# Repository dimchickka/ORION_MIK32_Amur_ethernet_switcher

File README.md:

Типы команд, поддерживаемые устройством

:SWITH0 1;SWITH2 1;\*OPC? - переключение нулевого реле в позицию 1, второго реле в позицию 1

:CHECK ALL;\*OPC? проверка всех реле

:CHECK 1;\*OPC?  -проверка реле 1

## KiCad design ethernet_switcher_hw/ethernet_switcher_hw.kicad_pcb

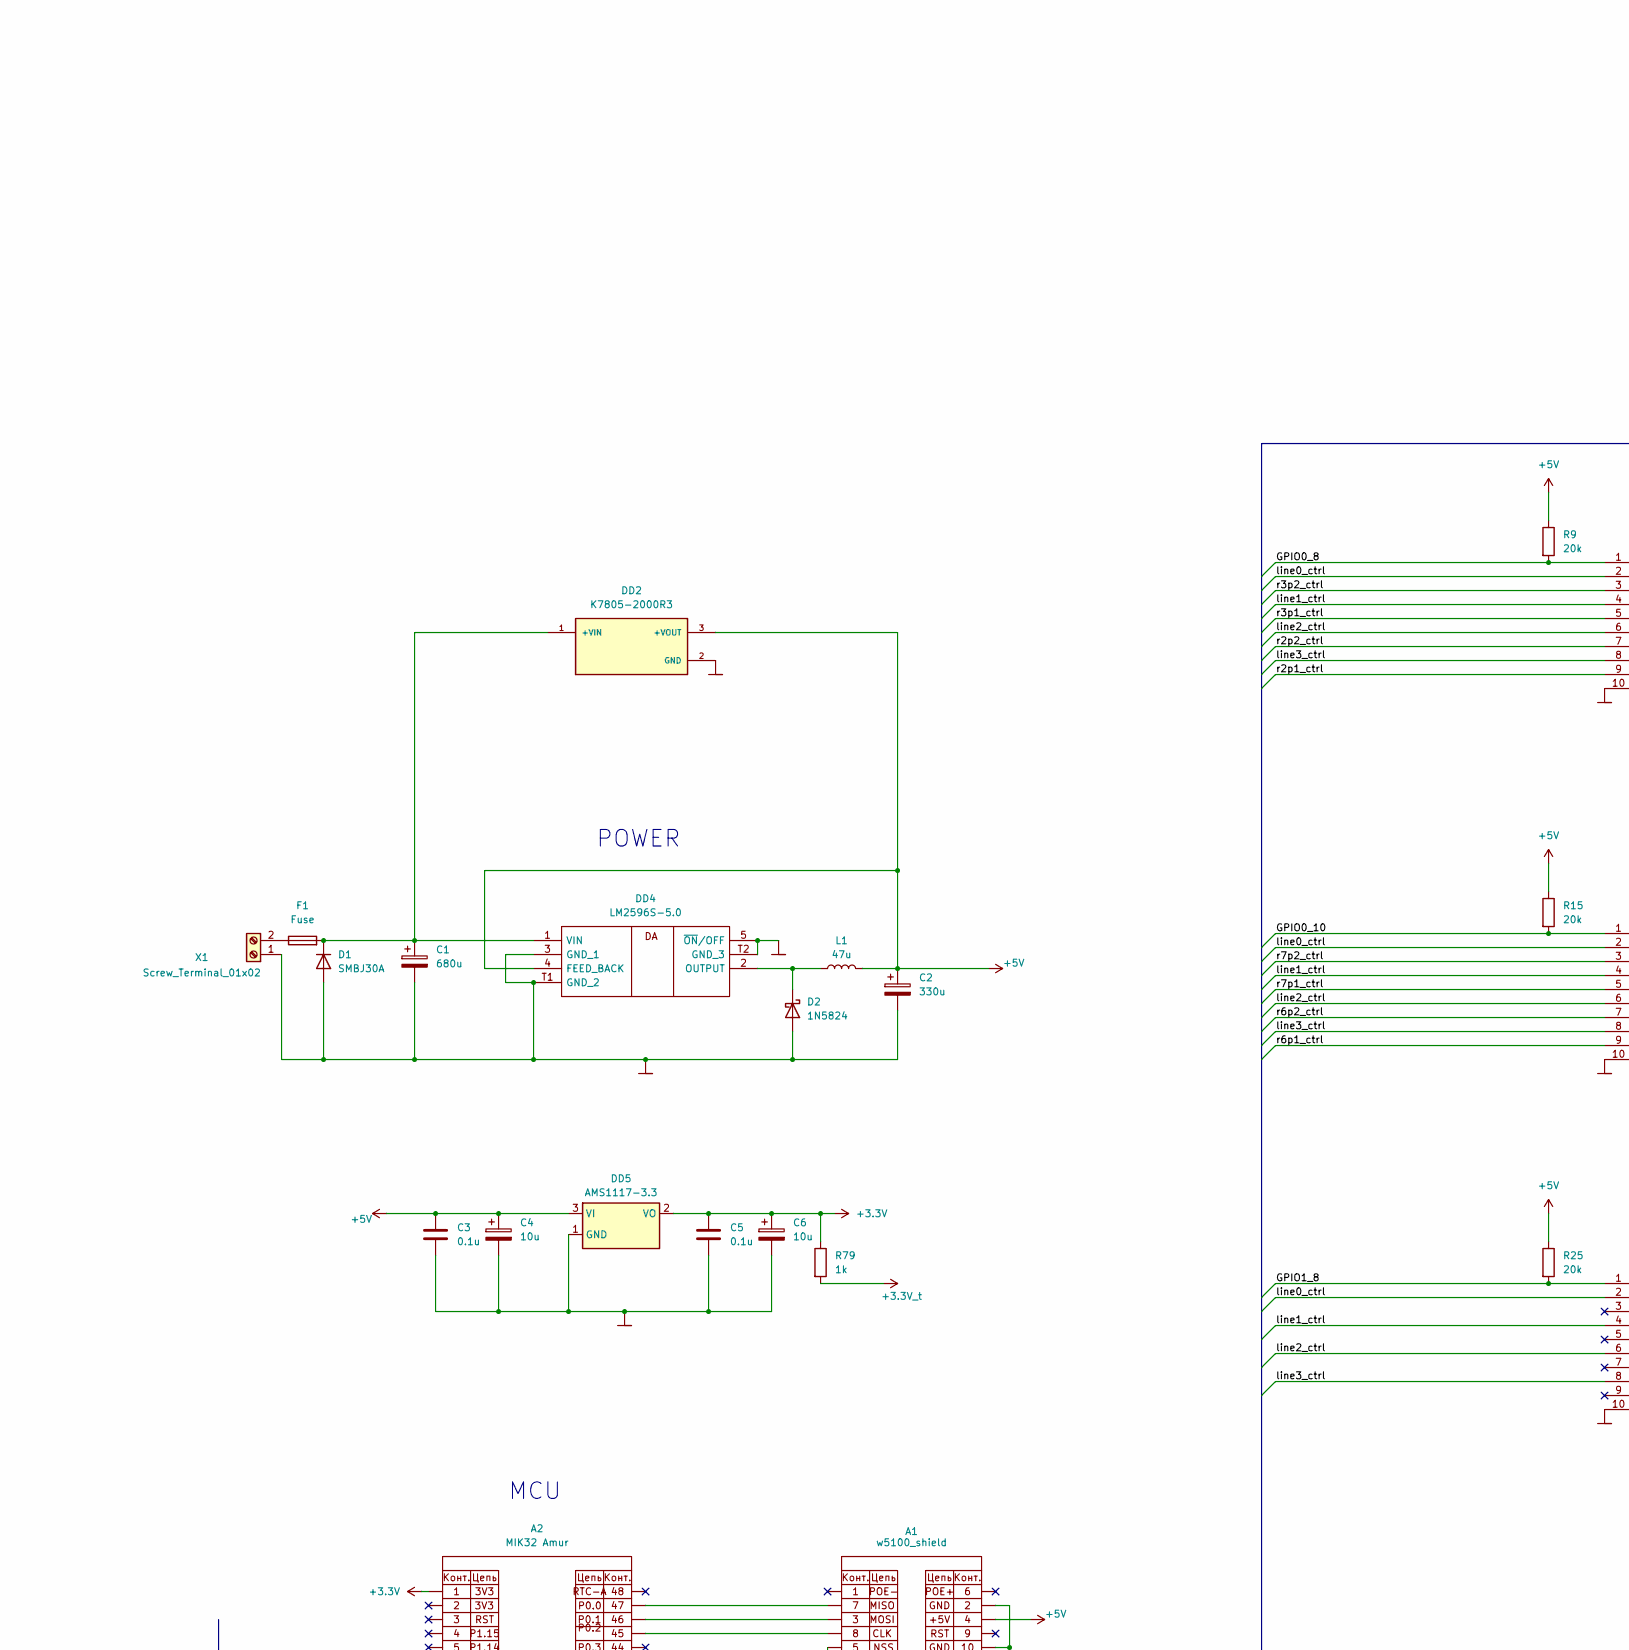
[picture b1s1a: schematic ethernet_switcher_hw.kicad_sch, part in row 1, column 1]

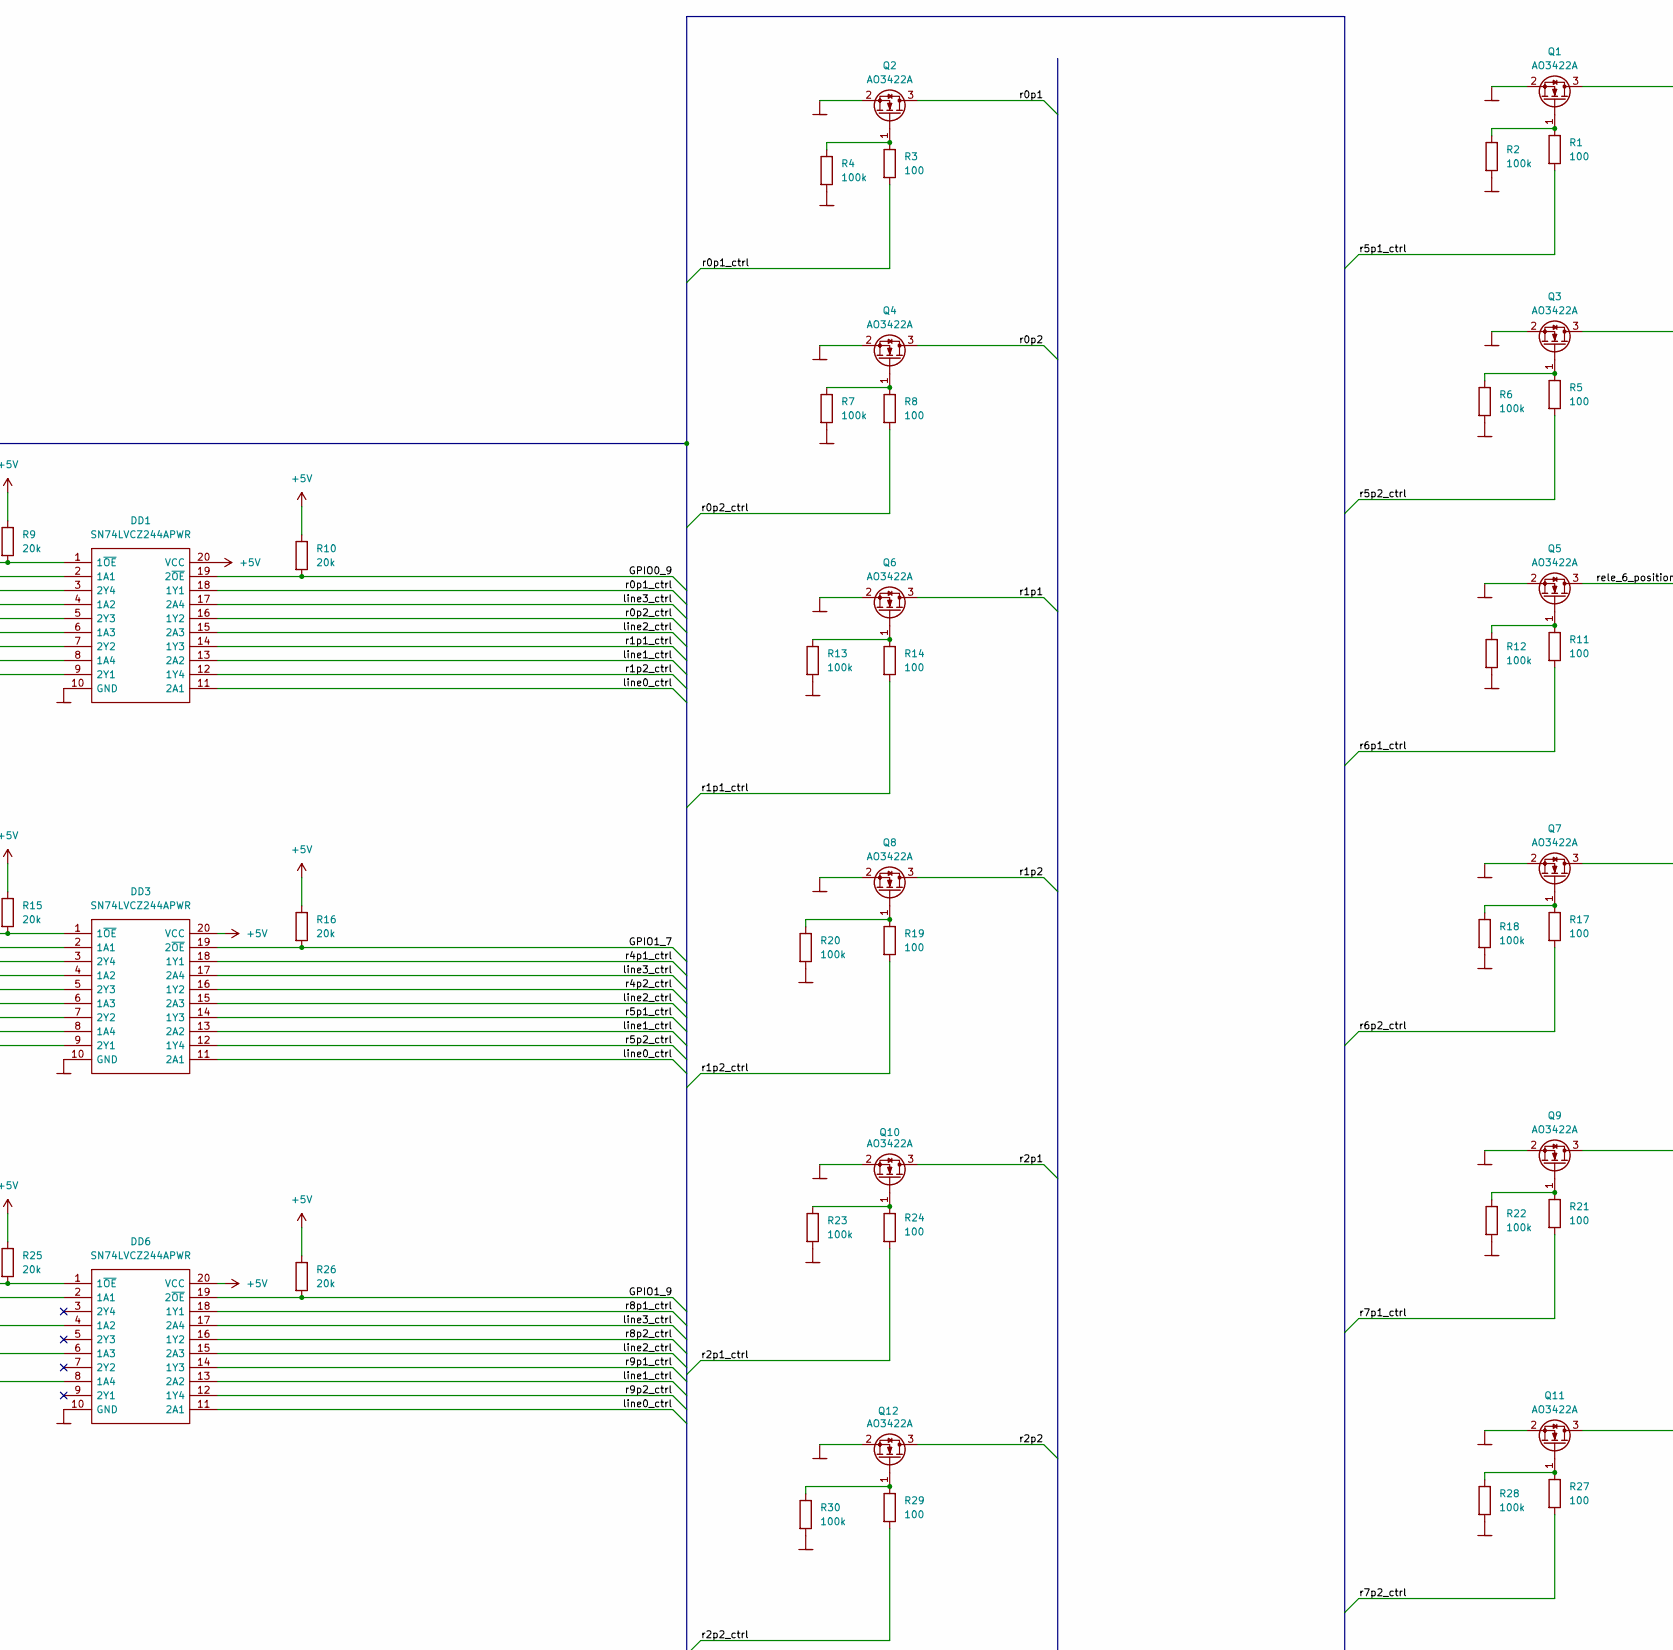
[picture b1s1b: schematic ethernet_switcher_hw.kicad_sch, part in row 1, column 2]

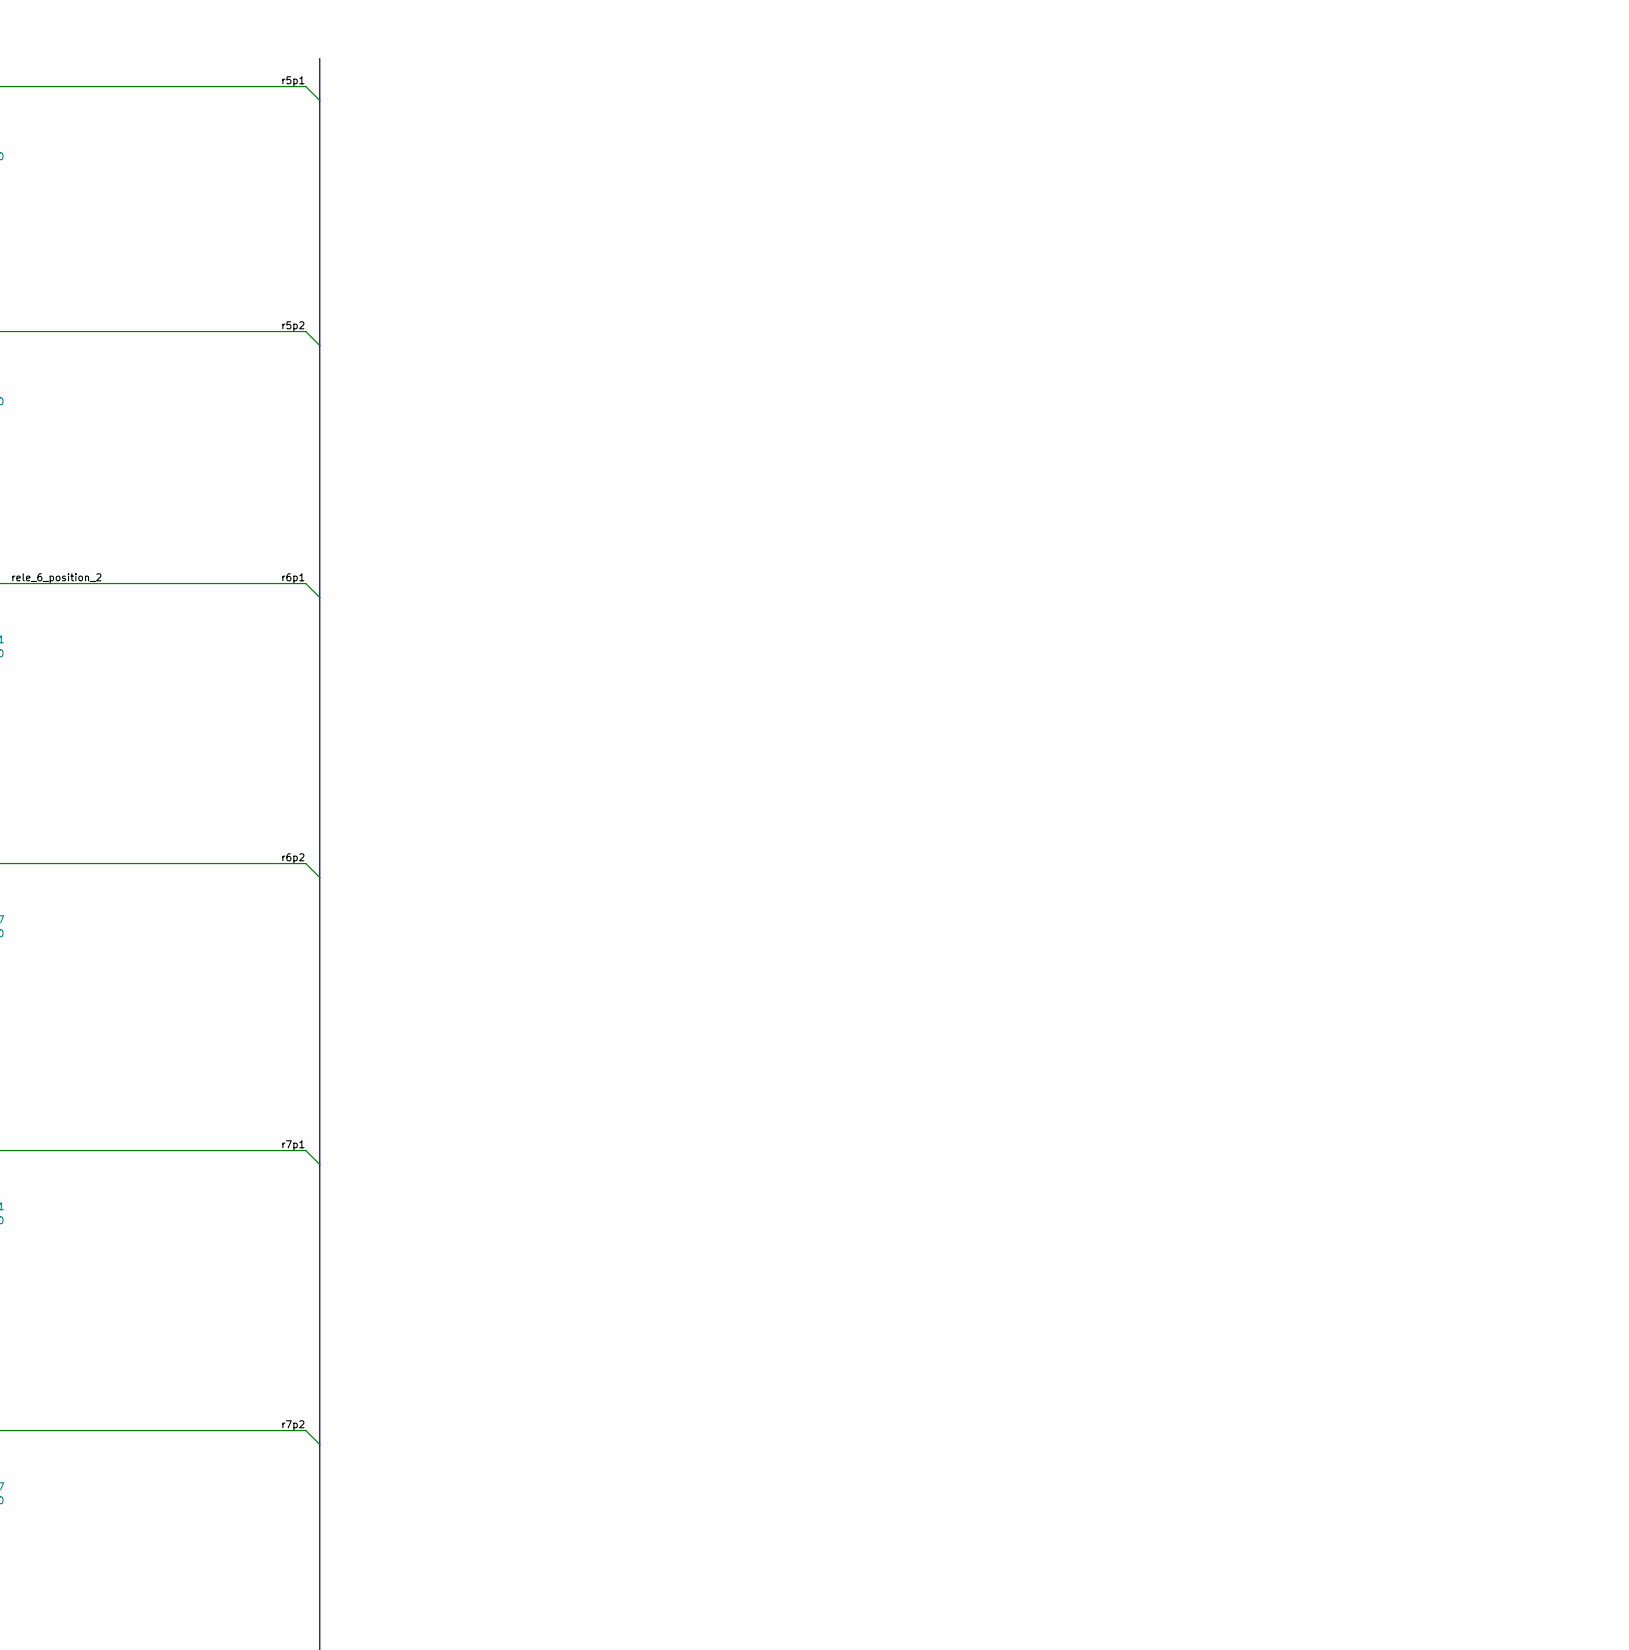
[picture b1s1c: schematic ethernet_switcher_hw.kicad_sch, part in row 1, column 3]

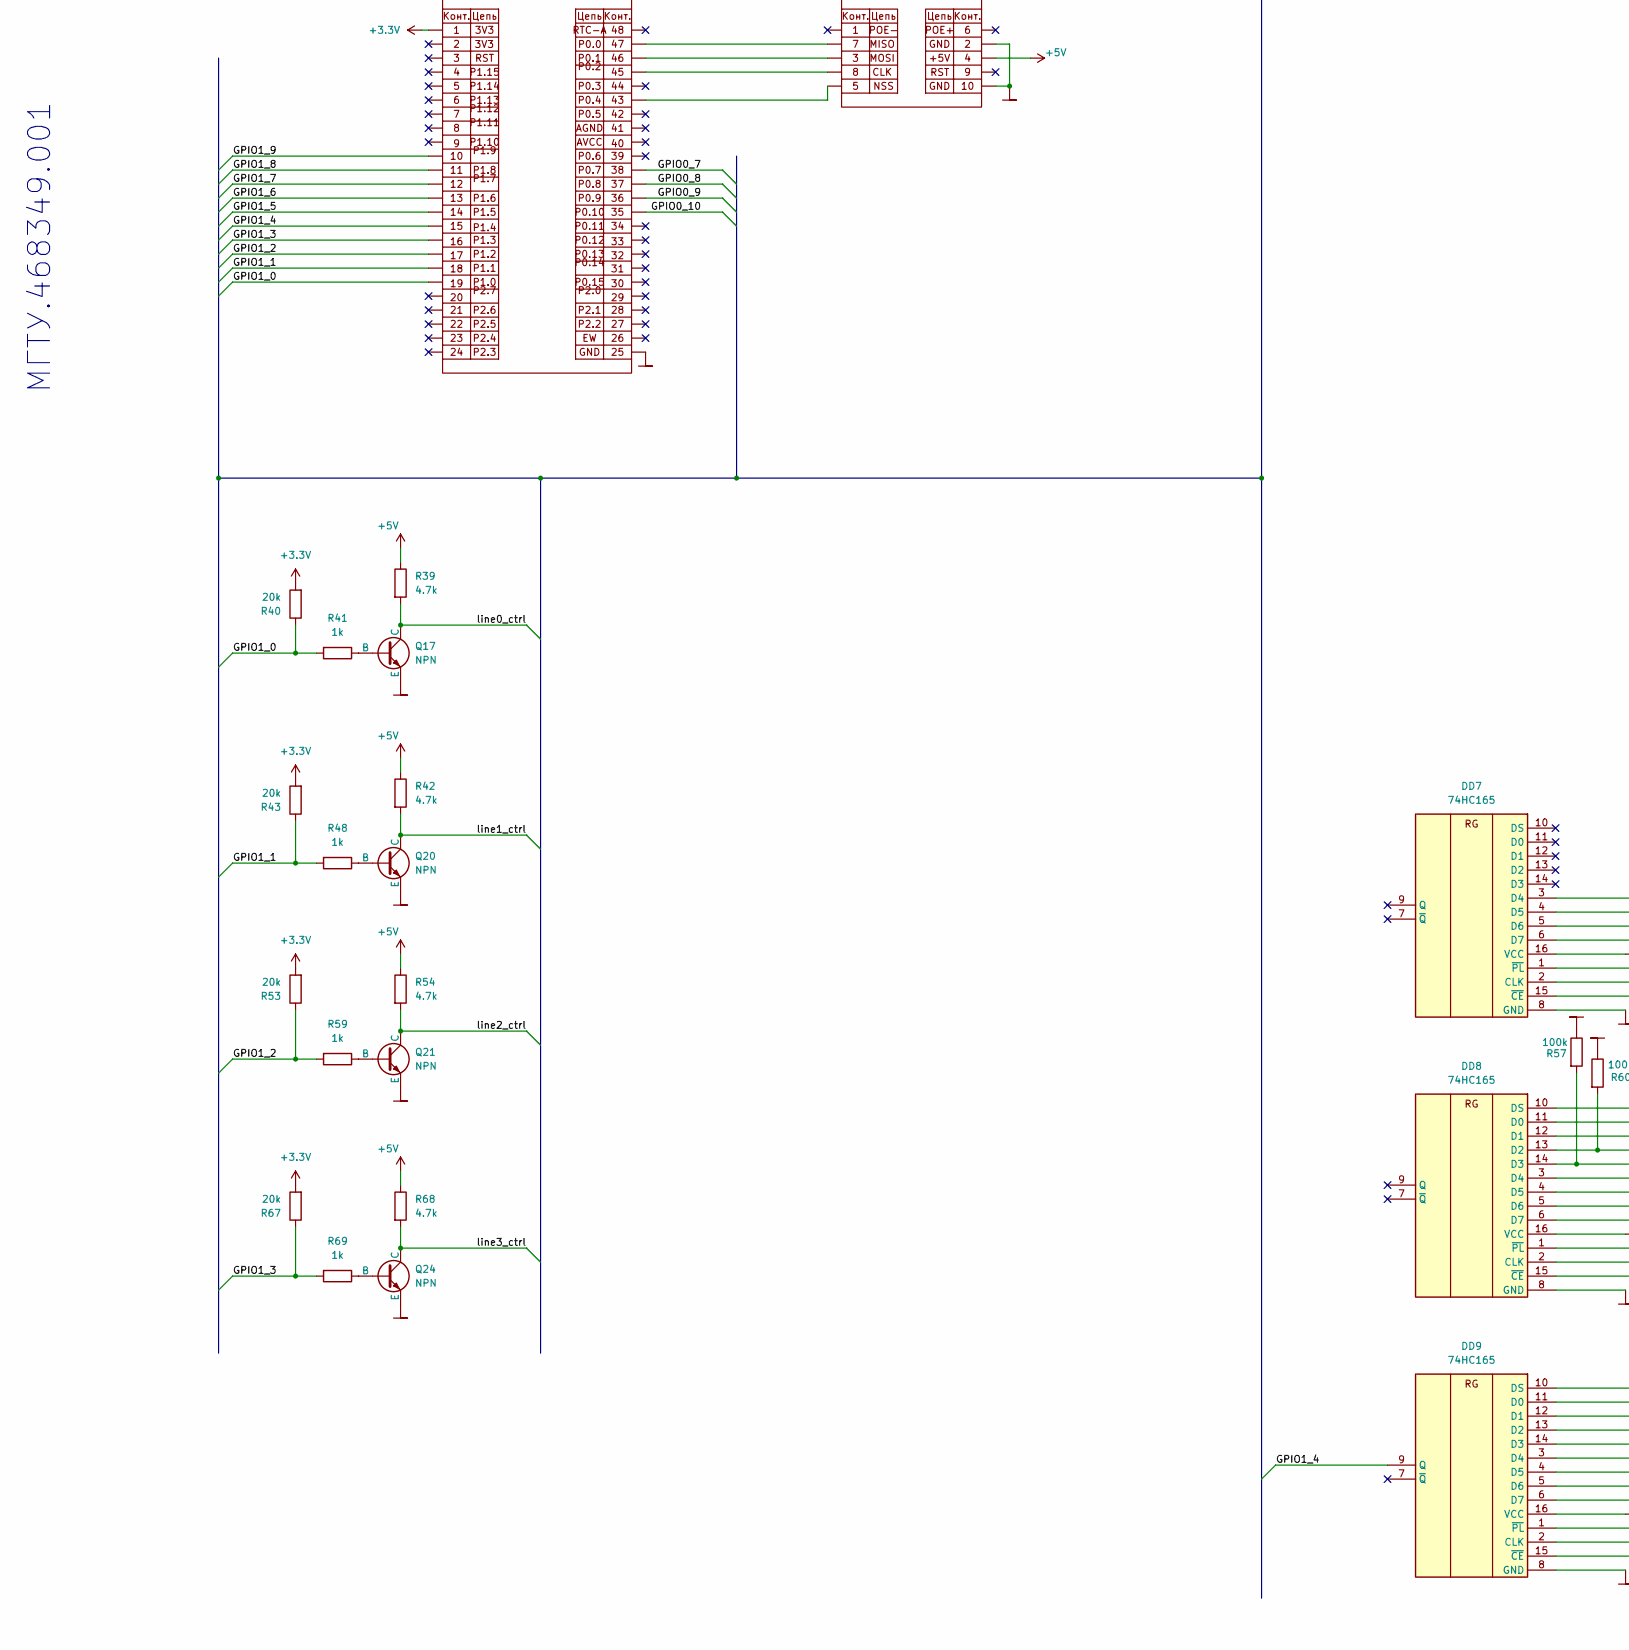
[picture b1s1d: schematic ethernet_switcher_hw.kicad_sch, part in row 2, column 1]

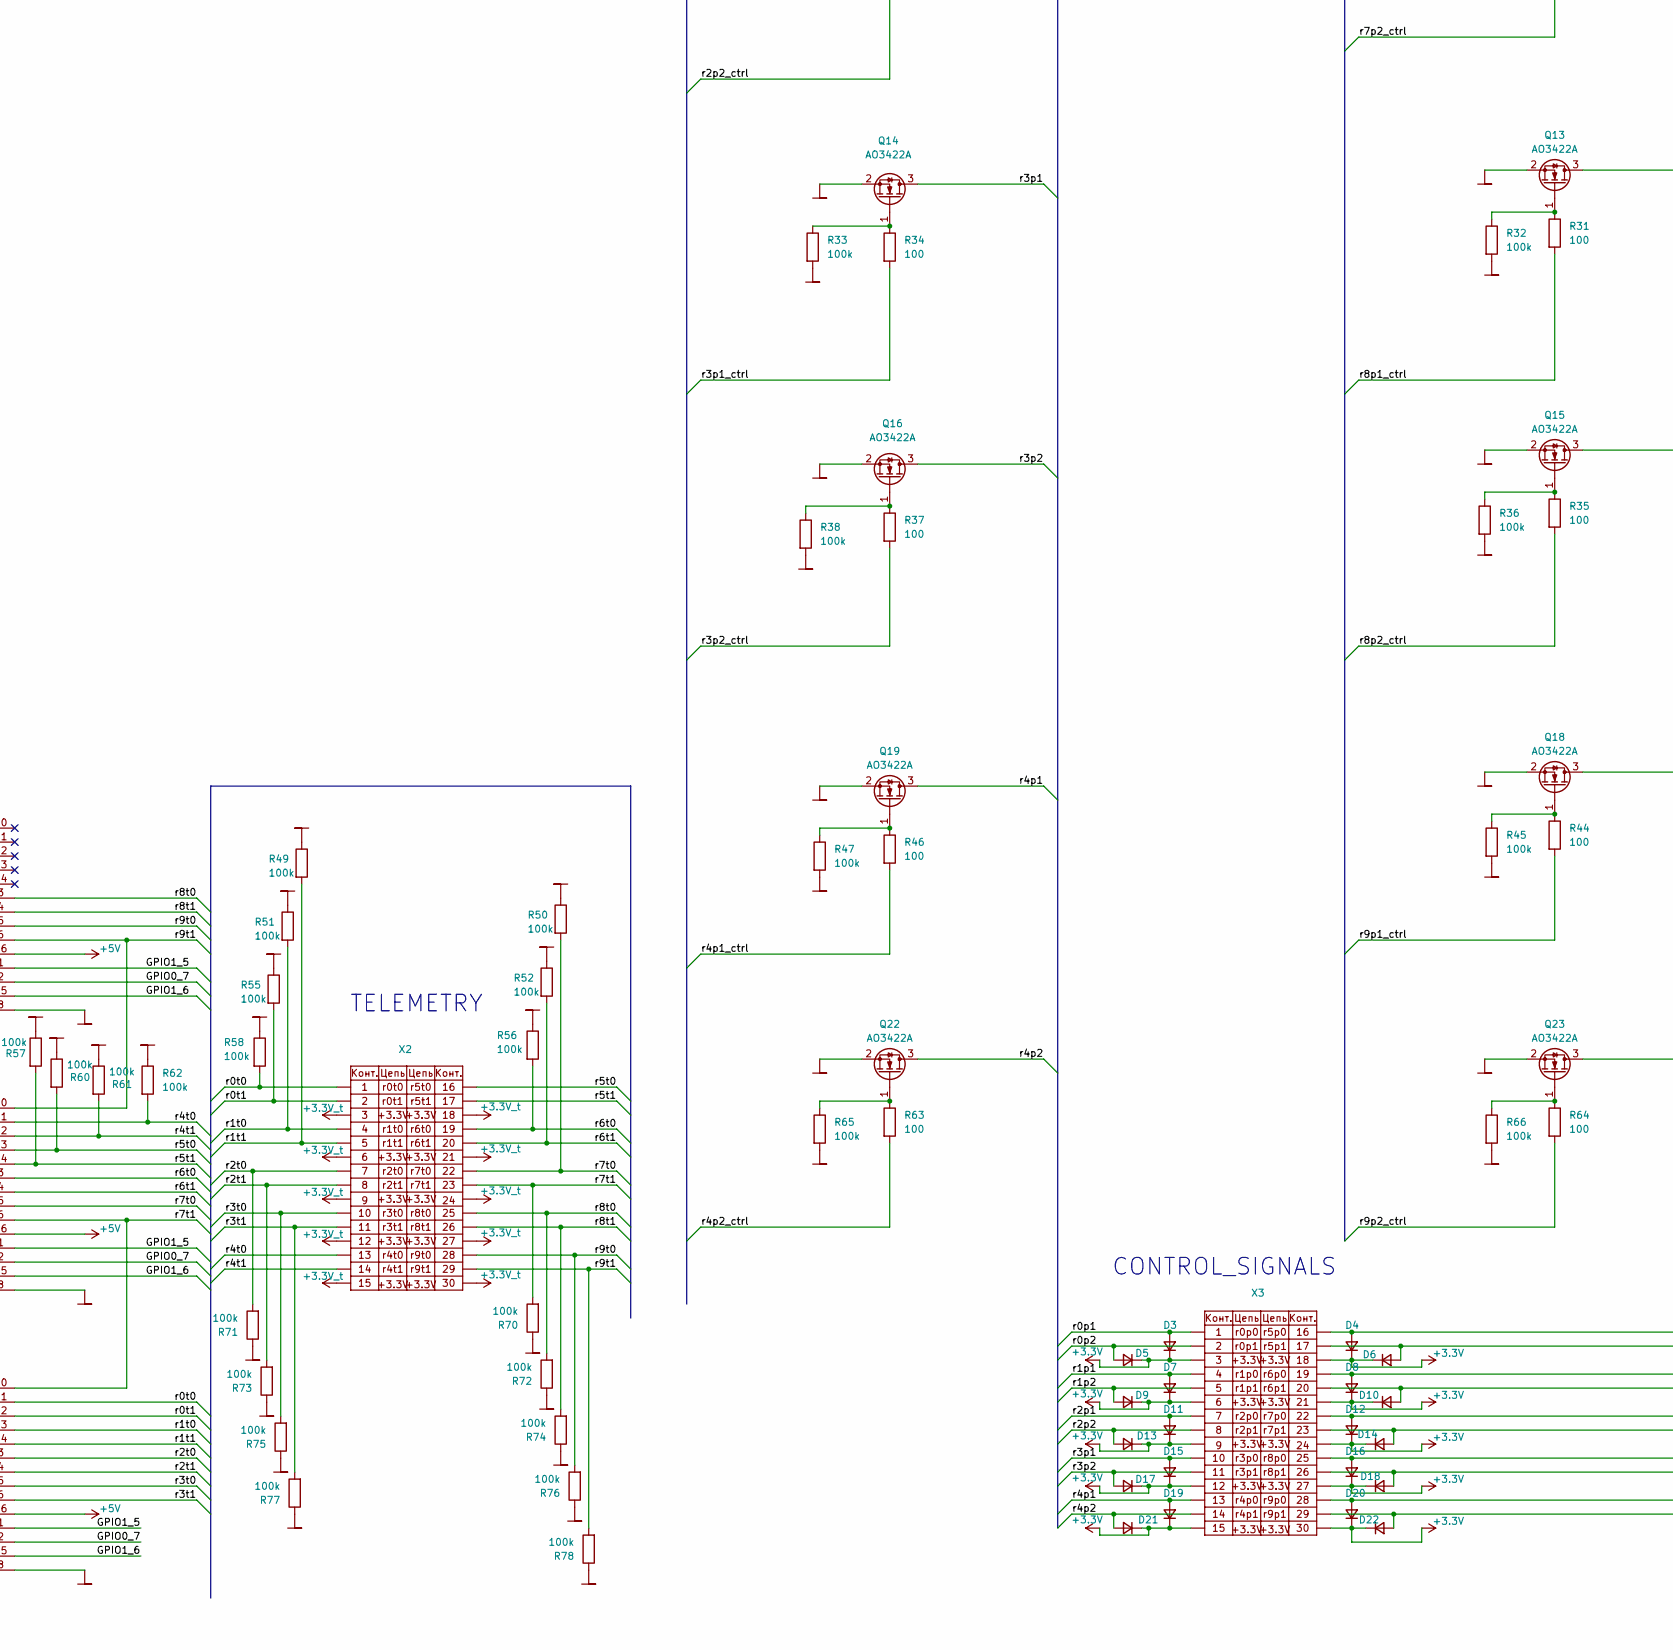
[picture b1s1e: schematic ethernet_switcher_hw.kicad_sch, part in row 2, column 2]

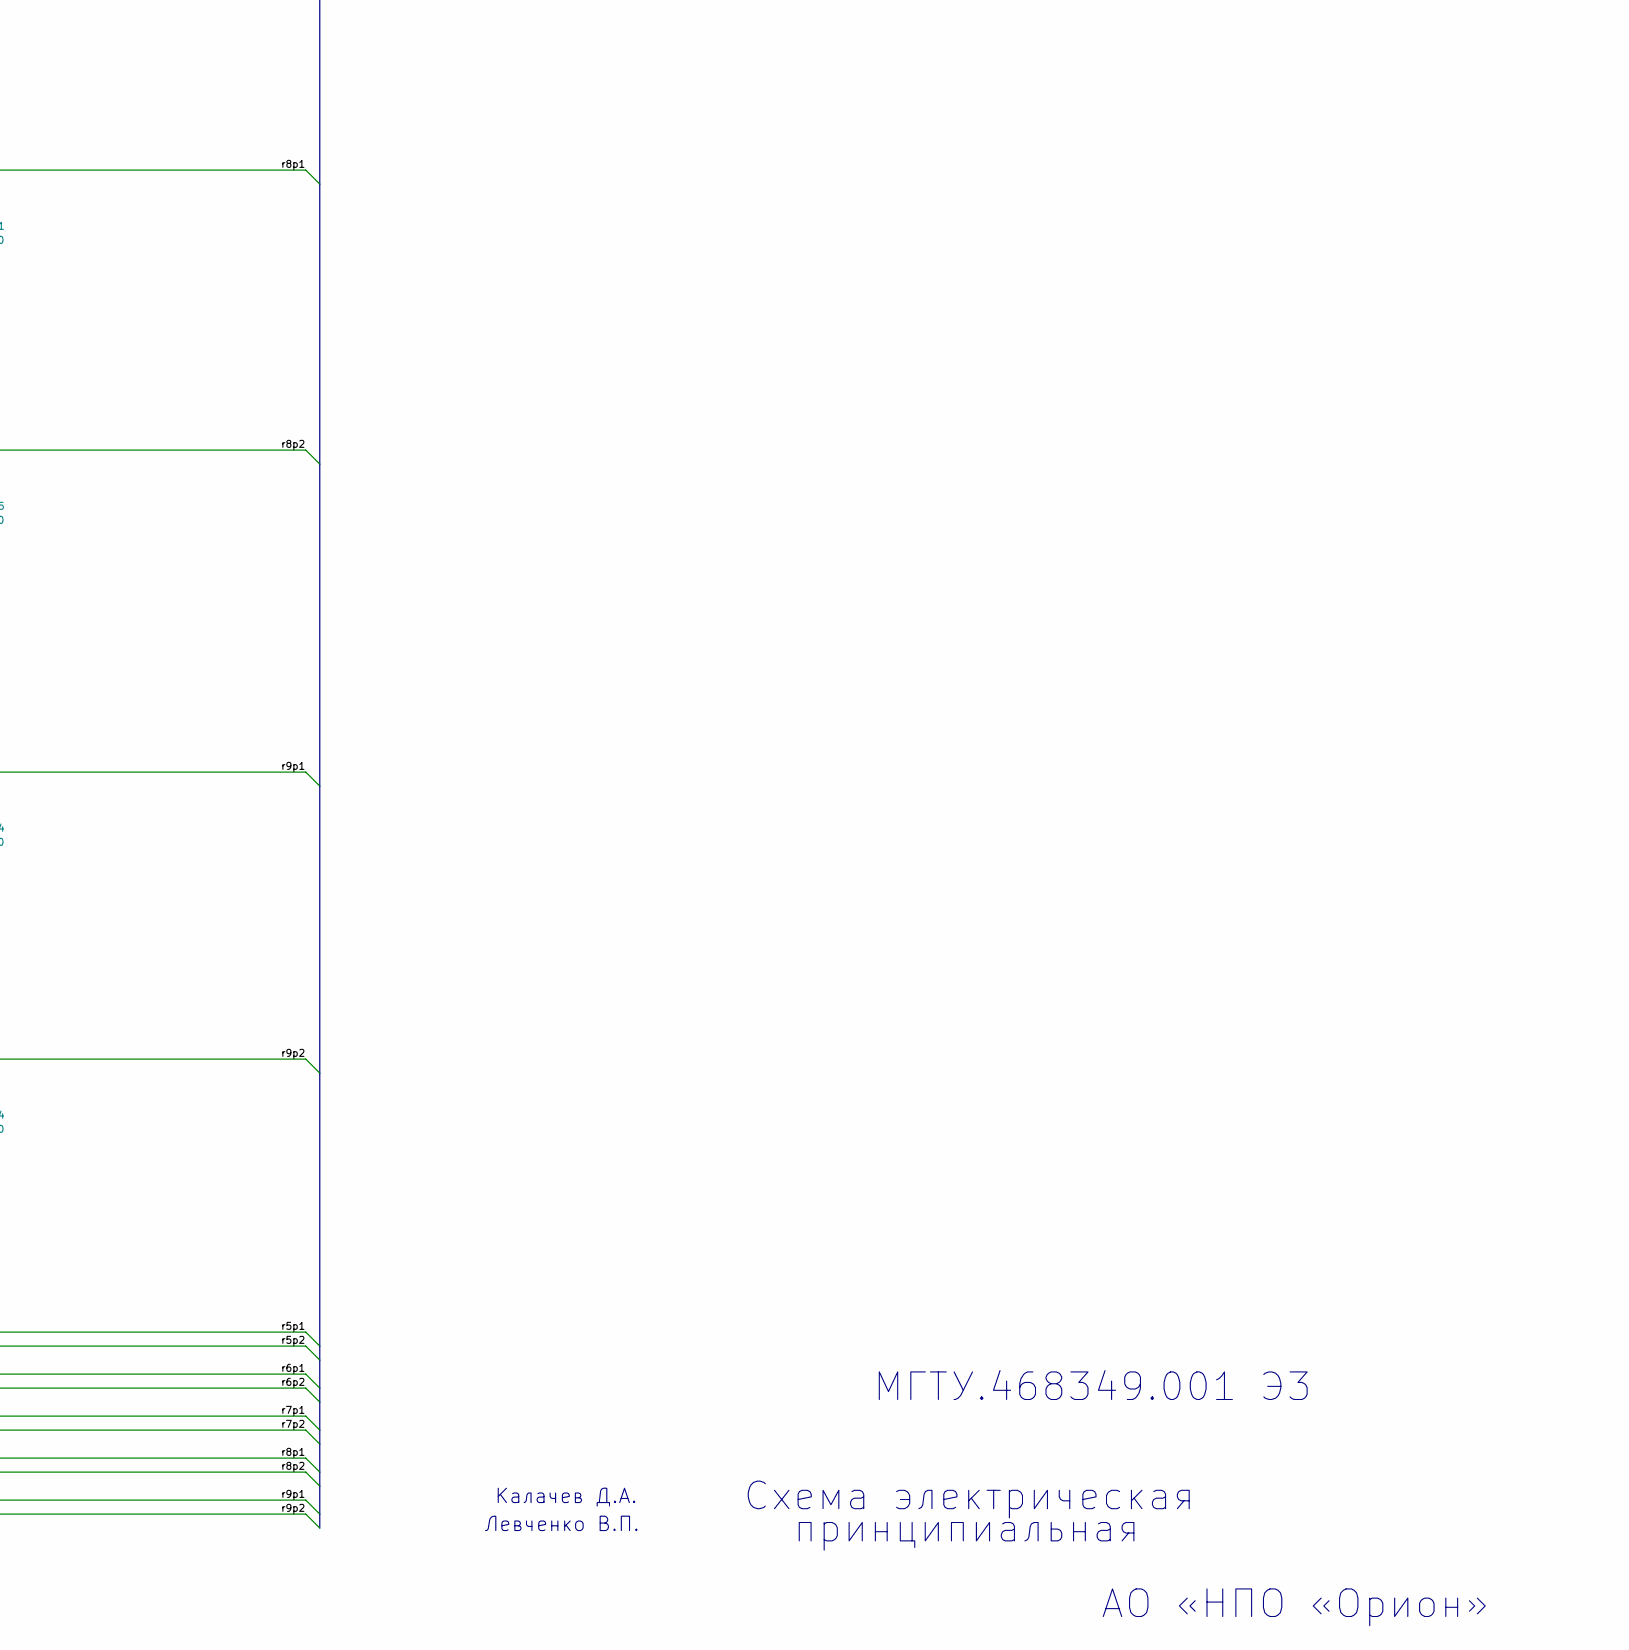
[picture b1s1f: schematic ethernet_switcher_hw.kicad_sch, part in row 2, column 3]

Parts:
A1: w5100_shield; forW5100Shield
A2: MIK32 Amur; dip_MIK32_Amur
C1: 680u; CP_Radial_D16.0mm_P7.50mm
C2: 330u; CP_EIA-7343-31_Kemet-D
C3, C5: 0.1u; C_1206_3216Metric
C4, C6: 10u; CAP_1206
D1: SMBJ30A; D_SMB
D2: 1N5824; D_DO-201AD_P15.24mm_Horizontal
D3, D4, D5, D6, D7, D8, D9, D10, D11, D12, D13, D14, D15, D16, D17, D18, D19, D20, D21, D22: 1N4148WS; D_SOD-323F
DD1, DD3, DD6: SN74LVCZ244APWR; DIP-20_W7.62mm; Manufacturer_Part_Number SN74LVCZ244APWR; Mouser Part Number 595-SN74LVCZ244APWR
DD2: K7805-2000R3; CONV_R-78B5.0-1.5; PARTREV 4
DD4: LM2596S-5.0; LM2596SXADJ; Manufacturer_Part_Number LM2596S-ADJ; Mouser Part Number 926-LM2596S-ADJ
DD5: AMS1117-3.3; SOT-223-3_TabPin2
DD7, DD8, DD9: 74HC165; DIP-16_W7.62mm
F1: Fuse; Fuse_Bourns_MF-SM_7.98x5.44mm
L1: 47u; L_12x12mm_H8mm
Q1, Q2, Q3, Q4, Q5, Q6, Q7, Q8, Q9, Q10, Q11, Q12, Q13, Q14, Q15, Q16, Q18, Q19, Q22, Q23: AO3422A; SOT-23_Handsoldering
Q17, Q20, Q21, Q24: NPN; SOT-23_Handsoldering
R1, R3, R5, R8, R11, R14, R17, R19, R21, R24, R27, R29, R31, R34, R35, R37, R44, R46, R63, R64: 100; R_0805_2012Metric
R2, R4, R6, R7, R12, R13, R18, R20, R22, R23, R28, R30, R32, R33, R36, R38, R45, R47, R49, R50, R51, R52, R55, R56, R57, R58, R60, R61, R62, R65, R66, R70, R71, R72, R73, R74, R75, R76, R77, R78: 100k; R_0805_2012Metric
R9, R10, R15, R16, R25, R26, R40, R43, R53, R67: 20k; R_0805_2012Metric
R39, R42, R54, R68: 4.7k; R_0805_2012Metric
R41, R48, R59, R69, R79: 1k; R_0805_2012Metric
X1: Screw_Terminal_01x02; TerminalBlock_Phoenix_MKDS-1,5-2-5.08_1x02_P5.08mm_Horizont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
X2, X3: PinHeader_2x15_P2.54mm_Vertical

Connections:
+5V: A1.4 (NSS), C2.1, C3.1, C4.1, DD1.20 (VCC), DD2.3 (+VOUT), DD3.20 (VCC), DD4.4 (FEED_BACK), DD5.3 (VI), DD6.20 (VCC), DD7.16 (VCC), DD8.16 (VCC), DD9.16 (VCC), L1.2, R9.1, R10.1, R15.1, R16.1, R25.1, R26.1, R39.1, R42.1, R54.1, R68.1
/GPIO0_7: A2.38 (P0.7), DD7.2 (CLK), DD8.2 (CLK), DD9.2 (CLK)
/GPIO0_8: A2.37 (P0.8), DD1.1 (1~OE), R9.2
/GPIO0_9: A2.36 (P0.9), DD1.19 (2~OE), R10.2
/GPIO0_10: A2.35 (P0.10), DD3.1 (1~OE), R15.2
/GPIO1_0: A2.19 (P1.0), R40.1, R41.2
/GPIO1_1: A2.18 (P1.1), R43.1, R48.2
/GPIO1_2: A2.17 (P1.2), R53.1, R59.2
/GPIO1_3: A2.16 (P1.3), R67.1, R69.2
/GPIO1_4: A2.15 (P1.4), DD9.9 (Q)
/GPIO1_5: A2.14 (P1.5), DD7.1 (~PL), DD8.1 (~PL), DD9.1 (~PL)
/GPIO1_6: A2.13 (P1.6), DD7.15 (~CE), DD8.15 (~CE), DD9.15 (~CE)
/GPIO1_7: A2.12 (P1.7), DD3.19 (2~OE), R16.2
/GPIO1_8: A2.11 (P1.8), DD6.1 (1~OE), R25.2
/GPIO1_9: A2.10 (P1.9), DD6.19 (2~OE), R26.2
/line0_ctrl: DD1.2 (1A1), DD1.11 (2A1), DD3.2 (1A1), DD3.11 (2A1), DD6.2 (1A1), DD6.11 (2A1), Q17.1 (C), R39.2
/line1_ctrl: DD1.4 (1A2), DD1.13 (2A2), DD3.4 (1A2), DD3.13 (2A2), DD6.4 (1A2), DD6.13 (2A2), Q20.1 (C), R42.2
/line2_ctrl: DD1.6 (1A3), DD1.15 (2A3), DD3.6 (1A3), DD3.15 (2A3), DD6.6 (1A3), DD6.15 (2A3), Q21.1 (C), R54.2
/line3_ctrl: DD1.8 (1A4), DD1.17 (2A4), DD3.8 (1A4), DD3.17 (2A4), DD6.8 (1A4), DD6.17 (2A4), Q24.1 (C), R68.2
/r0p1: D3.2 (A), Q2.3 (D), X3.1 (rop0)
/r0p1_ctrl: DD1.18 (1Y1), R3.2
/r0p2: D5.2 (A), Q4.3 (D), X3.2 (rop1)
/r0p2_ctrl: DD1.16 (1Y2), R8.2
/r0t0: DD9.11 (D0), R58.2, X2.1 (rot0)
/r0t1: DD9.12 (D1), R55.2, X2.2 (rot1)
/r1p1: D7.2 (A), Q6.3 (D), X3.4 (r1p0)
/r1p1_ctrl: DD1.14 (1Y3), R14.2
/r1p2: D9.2 (A), Q8.3 (D), X3.5 (r1p1)
/r1p2_ctrl: DD1.12 (1Y4), R19.2
/r1t0: DD9.13 (D2), R51.2, X2.4 (r1t0)
/r1t1: DD9.14 (D3), R49.2, X2.5 (r1t1)
/r2p1: D11.2 (A), Q10.3 (D), X3.7 (r2p0)
/r2p1_ctrl: DD1.9 (2Y1), R24.2
/r2p2: D13.2 (A), Q12.3 (D), X3.8 (r2p1)
/r2p2_ctrl: DD1.7 (2Y2), R29.2
/r2t0: DD9.3 (D4), R71.2, X2.7 (r2t0)
/r2t1: DD9.4 (D5), R73.2, X2.8 (r2t1)
/r3p1: D15.2 (A), Q14.3 (D), X3.10 (r3p0)
/r3p1_ctrl: DD1.5 (2Y3), R34.2
/r3p2: D17.2 (A), Q16.3 (D), X3.11 (r3p1)
/r3p2_ctrl: DD1.3 (2Y4), R37.2
/r3t0: DD9.5 (D6), R75.2, X2.10 (r3t0)
/r3t1: DD9.6 (D7), R77.2, X2.11 (r3t1)
/r4p1: D19.2 (A), Q19.3 (D), X3.13 (r4p0)
/r4p1_ctrl: DD3.18 (1Y1), R46.2
/r4p2: D21.2 (A), Q22.3 (D), X3.14 (r4p1)
/r4p2_ctrl: DD3.16 (1Y2), R63.2
/r4t0: DD8.11 (D0), R62.2, X2.13 (r4t0)
/r4t1: DD8.12 (D1), R61.2, X2.14 (r4t1)
/r5p1: D4.2 (A), Q1.3 (D), X3.16 (r5p0)
/r5p1_ctrl: DD3.14 (1Y3), R1.2
/r5p2: D6.2 (A), Q3.3 (D), X3.17 (r5p1)
/r5p2_ctrl: DD3.12 (1Y4), R5.2
/r5t0: DD8.13 (D2), R60.2, X2.16 (r5t0)
/r5t1: DD8.14 (D3), R57.2, X2.17 (r5t1)
/r6p1: D8.2 (A), Q5.3 (D), X3.19 (r6p0)
/r6p1_ctrl: DD3.9 (2Y1), R11.2
/r6p2: D10.2 (A), Q7.3 (D), X3.20 (r6p1)
/r6p2_ctrl: DD3.7 (2Y2), R17.2
/r6t0: DD8.3 (D4), R56.2, X2.19 (r6t0)
/r6t1: DD8.4 (D5), R52.2, X2.20 (r6t1)
/r7p1: D12.2 (A), Q9.3 (D), X3.22 (r7p0)
/r7p1_ctrl: DD3.5 (2Y3), R21.2
/r7p2: D14.2 (A), Q11.3 (D), X3.23 (r7p1)
/r7p2_ctrl: DD3.3 (2Y4), R27.2
/r7t0: DD8.5 (D6), R50.2, X2.22 (r7t0)
/r7t1: DD8.6 (D7), DD9.10 (DS), R70.2, X2.23 (r7t1)
/r8p1: D16.2 (A), Q13.3 (D), X3.25 (r8p0)
/r8p1_ctrl: DD6.18 (1Y1), R31.2
/r8p2: D18.2 (A), Q15.3 (D), X3.26 (r8p1)
/r8p2_ctrl: DD6.16 (1Y2), R35.2
/r8t0: DD7.3 (D4), R72.2, X2.25 (r8t0)
/r8t1: DD7.4 (D5), R74.2, X2.26 (r8p1)
/r9p1: D20.2 (A), Q18.3 (D), X3.28 (r9p0)
/r9p1_ctrl: DD6.14 (1Y3), R44.2
/r9p2: D22.2 (A), Q23.3 (D), X3.29 (r9p1)
/r9p2_ctrl: DD6.12 (1Y4), R64.2
/r9t0: DD7.5 (D6), R76.2, X2.28 (r9t0)
/r9t1: DD7.6 (D7), DD8.10 (DS), R78.2, X2.29 (r9t1)
GND: A1.2 (GND), A1.10 (GND), A2.25 (GND), C1.2, C2.2, C3.2, C4.2, C5.2, C6.2, D1.2 (A), D2.2 (A), DD1.10 (GND), DD2.2 (GND), DD3.10 (GND), DD4.3 (GND_1), DD4.5 (~ON/OFF), DD4.T1 (GND_2), DD4.T2 (GND_3), DD5.1 (GND), DD6.10 (GND), DD7.8 (GND), DD8.8 (GND), DD9.8 (GND), Q1.2 (S), Q2.2 (S), Q3.2 (S), Q4.2 (S), Q5.2 (S), Q6.2 (S), Q7.2 (S), Q8.2 (S), Q9.2 (S), Q10.2 (S), Q11.2 (S), Q12.2 (S), Q13.2 (S), Q14.2 (S), Q15.2 (S), Q16.2 (S), Q17.3 (E), Q18.2 (S), Q19.2 (S), Q20.3 (E), Q21.3 (E), Q22.2 (S), Q23.2 (S), Q24.3 (E), R2.2, R4.2, R6.2, R7.2, R12.2, R13.2, R18.2, R20.2, R22.2, R23.2, R28.2, R30.2, R32.2, R33.2, R36.2, R38.2, R45.2, R47.2, R49.1, R50.1, R51.1, R52.1, R55.1, R56.1, R57.1, R58.1, R60.1, R61.1, R62.1, R65.2, R66.2, R70.1, R71.1, R72.1, R73.1, R74.1, R75.1, R76.1, R77.1, R78.1, X1.1
unnamed: A1.5 (+5V), A2.43 (P0.4)
unnamed: A1.8 (CLK), A2.45 (P0.2)
unnamed: A1.7 (MISO), A2.47 (P0.0)
unnamed: A1.3 (MOSI), A2.46 (P0.1)
unnamed: C1.1, D1.1 (K), DD2.1 (+VIN), DD4.1 (VIN), F1.2
unnamed: D2.1 (K), DD4.2 (OUTPUT), L1.1
unnamed: Q1.1 (G), R1.1, R2.1
unnamed: Q2.1 (G), R3.1, R4.1
unnamed: Q3.1 (G), R5.1, R6.1
unnamed: Q4.1 (G), R7.1, R8.1
unnamed: Q5.1 (G), R11.1, R12.1
unnamed: Q6.1 (G), R13.1, R14.1
unnamed: Q7.1 (G), R17.1, R18.1
unnamed: Q8.1 (G), R19.1, R20.1
unnamed: Q9.1 (G), R21.1, R22.1
unnamed: Q10.1 (G), R23.1, R24.1
unnamed: Q11.1 (G), R27.1, R28.1
unnamed: Q12.1 (G), R29.1, R30.1
unnamed: Q13.1 (G), R31.1, R32.1
unnamed: Q14.1 (G), R33.1, R34.1
unnamed: Q15.1 (G), R35.1, R36.1
unnamed: Q16.1 (G), R37.1, R38.1
unnamed: Q17.2 (B), R41.1
unnamed: Q18.1 (G), R44.1, R45.1
unnamed: Q19.1 (G), R46.1, R47.1
unnamed: Q20.2 (B), R48.1
unnamed: Q21.2 (B), R59.1
unnamed: Q22.1 (G), R63.1, R65.1
unnamed: Q23.1 (G), R64.1, R66.1
unnamed: Q24.2 (B), R69.1
unnamed: F1.1, X1.2

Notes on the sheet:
MCU
Калачев Д.А.
принципиальная
POWER
МГТУ.468349.001
CONTROL_SIGNALS
АО «НПО «Орион»
Схема электрическая
Левченко В.П.
TELEMETRY
МГТУ.468349.001 Э3

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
